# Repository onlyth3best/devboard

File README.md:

# devboard
a project for Fallout, made with help from stasis.hackclub.com/starter-projects/devboard
<br/> /kicad has relevant KiCad files, /3dmodels has the .STEP files, /prod has gerber files~
<br/>
<br/> "_A development board is a specially designed printed circuit board (PCB) that integrates a microcontroller or microprocessor along with essential components such as input/output pins, power supply interfaces, USB connectors, LEDs, and often onboard sensors._" ([source](https://regentelectronics.com/microcontrollers/what-is-a-development-board-introduction-types-and-applications))
<br/>
<br/>

<br/> Setup guide:
<br/>  - the only setup needed in this sense, if I understand correctly, is using the files in this repo to upload to JLCPCB or something similar in order to receive a physical version…
<br/>
<br/> Motivation:
<br/>  - Since I started hardware very very recently, I wanted to try my hand at something that was a little more challenging than a regular pcb but still within the realm of KiCad work. Additionally, I find routing very fun to do, hence why I had a lot of fun with this project in certain parts.

<br/> BOM:
<br/>
| Reference  | Qty | Value | approx price in USD | links I found, not sure if they're all 100% correct though :heavysob: |
| ------------- | ------------- | ------------- | ------------- | ------------- |
| C1, C10 | 2 | C_0402_1005Metric | 0.02 | [links](https://www.kondik.cz/cl05a105kp5nnnc/) |
| C2, C3, C4, C5, C6, C7, C8, C9, C11, C12 | 10 | C_0402_1005Metric | 0.10| [links](https://www.kondik.cz/cl05a105kp5nnnc/) |
| C13, C14 | 2 | C_0402_1005Metric | 0.02 | [links](https://www.kondik.cz/cc0402krx7r7bb104-kondenzator-keramicky-smd-0402-100nf-16v/) |
| C15, C16 | 2 | C_0402_1005Metric | 0.02 | [links](https://www.kondik.cz/cc0402krx7r7bb104-kondenzator-keramicky-smd-0402-100nf-16v/) |
| J1 | 1 | USB_C_Receptacle_HRO_TYPE-C-31-M-12 | 0.10–0.25 | [links](https://www.lcsc.com/product-detail/USB-Type-C_Korean-Hroparts-Elec-TYPE-C-31-M-12_C165948.html) |
| J2, J3 | 2 | PinHeader_1x20_P2.54mm_Vertical | 0.20–0.80 | [links](https://www.lcsc.com/search?q=1x20+2.54mm+pin+header) |
| J4 | 1 | R_0402_1005Metric | 0.01 | [links](https://www.lcsc.com/search?q=0402+resistor) |
| R1, R2 | 2 | R_0402_1005Metric | 0.02 | [links](https://www.digikey.com/en/products/filter/resistor-kits/129) |
| R3, R4 | 2 | R_0402_1005Metric | 0.02 | [links](https://www.digikey.com/en/products/filter/resistor-kits/129) |
| R5, R7 | 2 | R_0402_1005Metric | 0.02 | [links](https://www.digikey.com/en/products/filter/resistor-kits/129) |
| R6 | 1 | R_0402_1005Metric | 0.01 | [links](https://www.digikey.com/en/products/filter/resistor-kits/129) |
| SW1 | 1 | SW_Push_SPST_NO_Alps_SKRK | 0.10–0.50 | [links](https://www.lcsc.com/search?q=Alps+SKRK) |
| U1 | 1 | QFN-56-1EP_7x7mm_P0.4mm_EP3.2x3.2mm | 1.00–2.00 | [links](https://www.raspberrypi.com/products/rp2040) |
| U3 | 1 | SOIC-8_5.3x5.3mm_P1.27mm | 0.30–0.80 | [links](https://www.lcsc.com/product-detail/NOR-FLASH_Winbond-Elec-W25Q64JVSSIQ_C179171.html) |
| U4 | 1 | TO-92_Inline | 0.05–0.30 | [links](https://www.lcsc.com/product-detail/Bipolar-Transistors-BJT_ON-Semicon-2N3904_C20526.html) |
| Y1 | 1 | Crystal_SMD_3225-4Pin_3.2x2.5mm | 0.05–0.20  | [links](https://www.lcsc.com/product-detail/C13738.html) |
|  |  |  | total BOM price ~ 2.95, with JLCPCB cost it's around 5.95 USD |  |

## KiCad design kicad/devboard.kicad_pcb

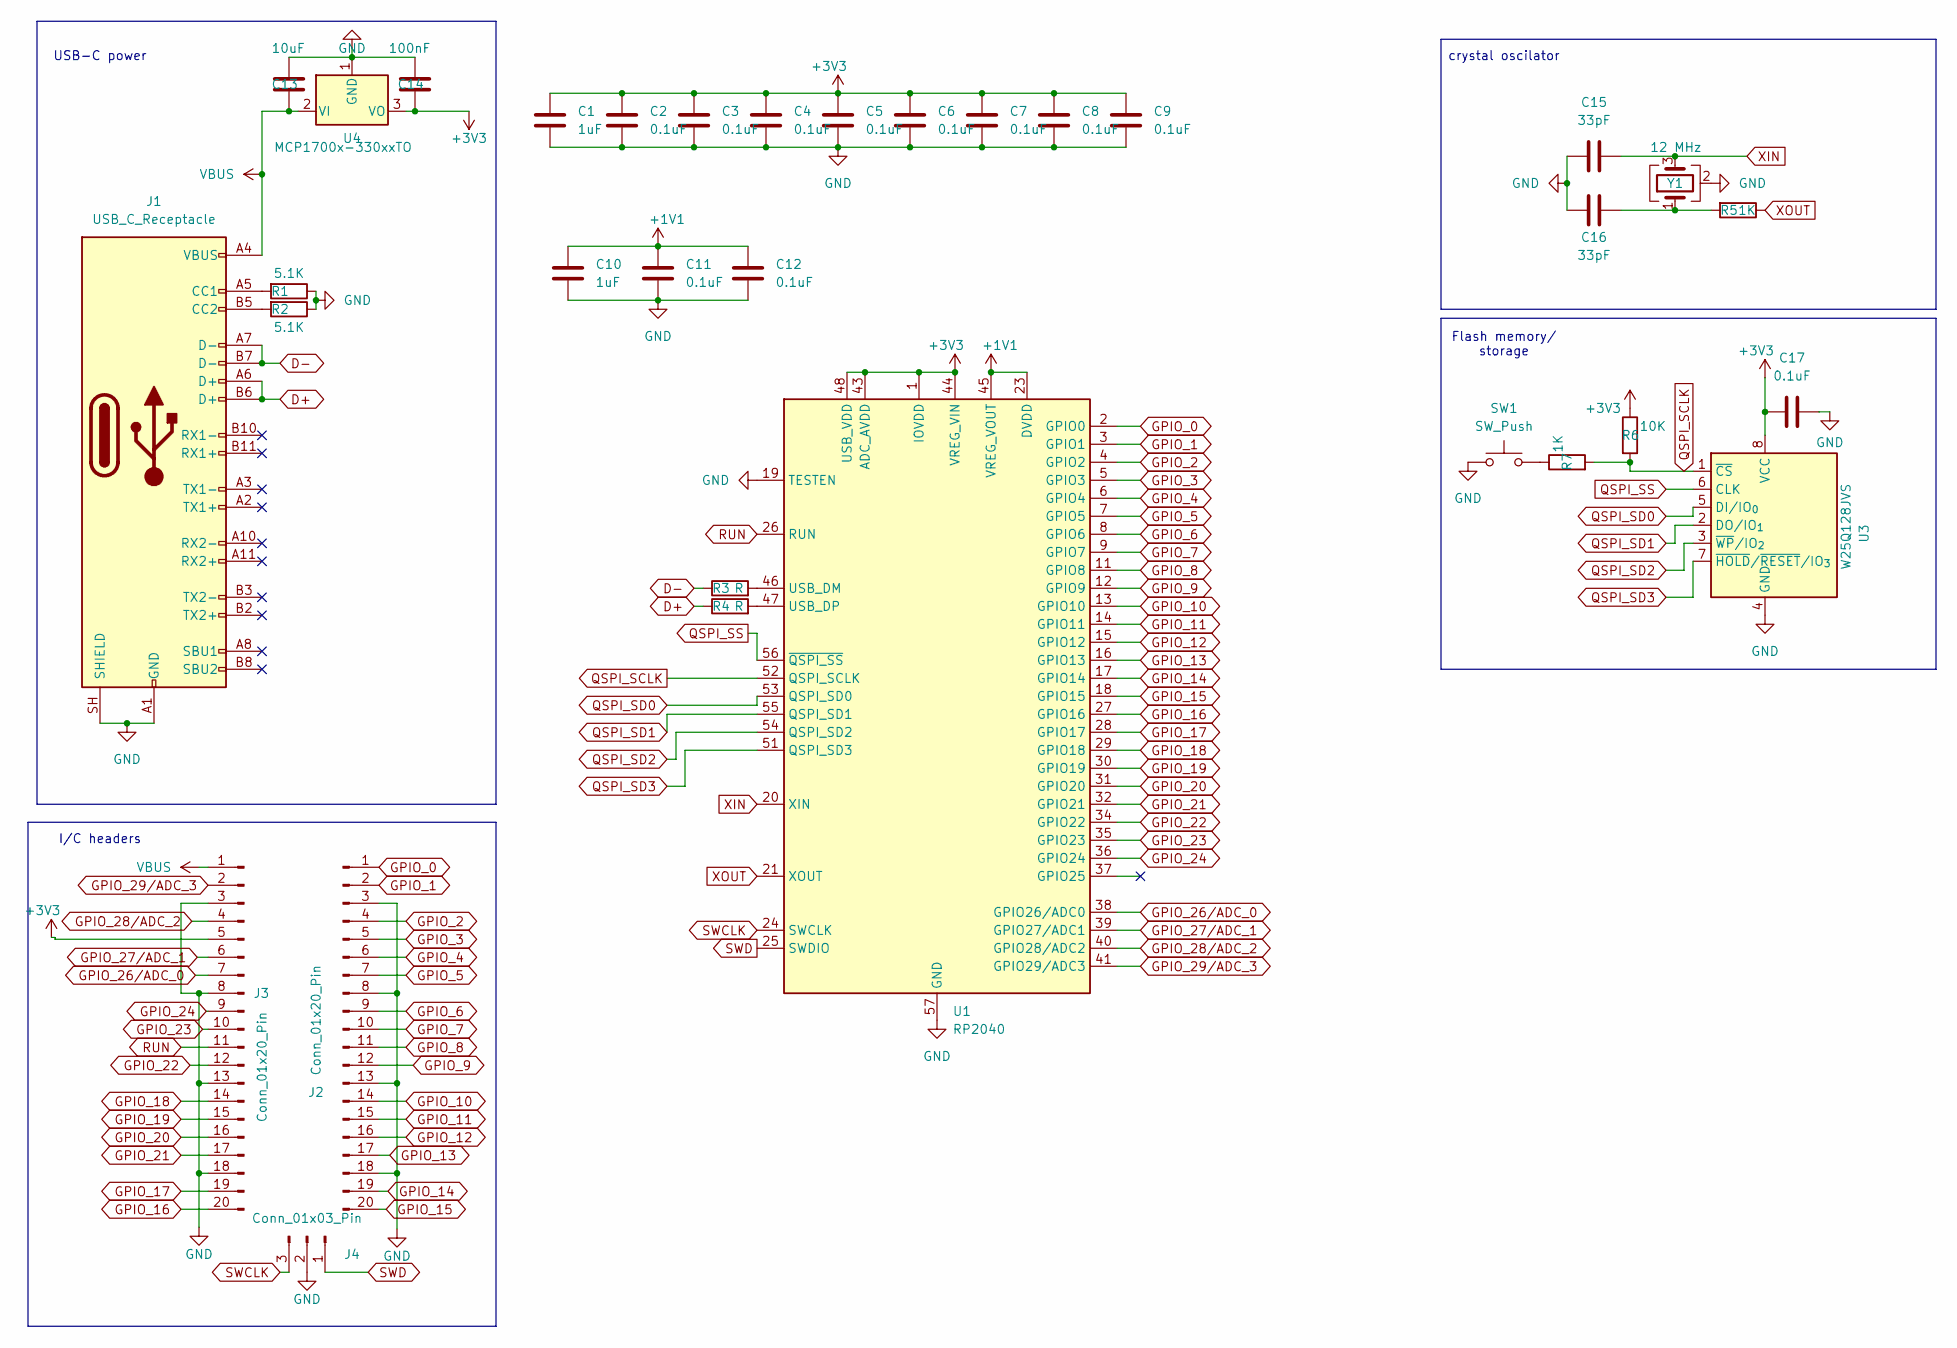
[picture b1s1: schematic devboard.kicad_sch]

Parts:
C1, C10: 1uF; C_0402_1005Metric
C2, C3, C4, C5, C6, C7, C8, C9, C11, C12, C17: 0.1uF; C_0402_1005Metric
C13: 10uF; C_0402_1005Metric
C14: 100nF; C_0402_1005Metric
C15, C16: 33pF; C_0402_1005Metric
J1: USB_C_Receptacle; USB_C_Receptacle_HRO_TYPE-C-31-M-12
J2, J3: Conn_01x20_Pin; PinHeader_1x20_P2.54mm_Vertical
J4: Conn_01x03_Pin; PinHeader_1x03_P2.54mm_Vertical
R1, R2: 5.1K; R_0402_1005Metric
R3, R4: R; R_0402_1005Metric
R5, R7: 1K; R_0402_1005Metric
R6: 10K; R_0402_1005Metric
SW1: SW_Push; SW_Push_SPST_NO_Alps_SKRK
U1: RP2040; QFN-56-1EP_7x7mm_P0.4mm_EP3.2x3.2mm
U3: W25Q128JVS; SOIC-8_5.3x5.3mm_P1.27mm
U4: MCP1700x-330xxTO; TO-92_Inline
Y1: 12 MHz; Crystal_SMD_3225-4Pin_3.2x2.5mm

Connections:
+1V1: C10.1, C11.1, C12.1, U1.23 (DVDD), U1.45 (VREG_VOUT), U1.50 (DVDD)
+3V3: C1.1, C2.1, C3.1, C4.1, C5.1, C6.1, C7.1, C8.1, C9.1, C14.2, C17.1, J3.5, R6.1, U1.1 (IOVDD), U1.10 (IOVDD), U1.22 (IOVDD), U1.33 (IOVDD), U1.42 (IOVDD), U1.43 (ADC_AVDD), U1.44 (VREG_VIN), U1.48 (USB_VDD), U1.49 (IOVDD), U3.8 (VCC), U4.3 (VO)
D+: J1.A6 (D+), J1.B6 (D+), R4.1
D-: J1.A7 (D-), J1.B7 (D-), R3.1
GND: C1.2, C2.2, C3.2, C4.2, C5.2, C6.2, C7.2, C8.2, C9.2, C10.2, C11.2, C12.2, C13.1, C14.1, C15.1, C16.1, C17.2, J1.A1 (GND), J1.A12 (GND), J1.B1 (GND), J1.B12 (GND), J1.SH (SHIELD), J2.3, J2.8, J2.13, J2.18, J3.3, J3.8, J3.13, J3.18, J4.2, R1.1, R2.1, SW1.1, U1.19 (TESTEN), U1.57 (GND), U3.4 (GND), U4.1 (GND), Y1.2 (G), Y1.4 (G)
GPIO_0: J2.1, U1.2 (GPIO0)
GPIO_1: J2.2, U1.3 (GPIO1)
GPIO_2: J2.4, U1.4 (GPIO2)
GPIO_3: J2.5, U1.5 (GPIO3)
GPIO_4: J2.6, U1.6 (GPIO4)
GPIO_5: J2.7, U1.7 (GPIO5)
GPIO_6: J2.9, U1.8 (GPIO6)
GPIO_7: J2.10, U1.9 (GPIO7)
GPIO_8: J2.11, U1.11 (GPIO8)
GPIO_9: J2.12, U1.12 (GPIO9)
GPIO_10: J2.14, U1.13 (GPIO10)
GPIO_11: J2.15, U1.14 (GPIO11)
GPIO_12: J2.16, U1.15 (GPIO12)
GPIO_13: J2.17, U1.16 (GPIO13)
GPIO_14: J2.19, U1.17 (GPIO14)
GPIO_15: J2.20, U1.18 (GPIO15)
GPIO_16: J3.20, U1.27 (GPIO16)
GPIO_17: J3.19, U1.28 (GPIO17)
GPIO_18: J3.14, U1.29 (GPIO18)
GPIO_19: J3.15, U1.30 (GPIO19)
GPIO_20: J3.16, U1.31 (GPIO20)
GPIO_21: J3.17, U1.32 (GPIO21)
GPIO_22: J3.12, U1.34 (GPIO22)
GPIO_23: J3.10, U1.35 (GPIO23)
GPIO_24: J3.9, U1.36 (GPIO24)
GPIO_26/ADC_0: J3.7, U1.38 (GPIO26/ADC0)
GPIO_27/ADC_1: J3.6, U1.39 (GPIO27/ADC1)
GPIO_28/ADC_2: J3.4, U1.40 (GPIO28/ADC2)
GPIO_29/ADC_3: J3.2, U1.41 (GPIO29/ADC3)
unnamed: C16.2, R5.2, Y1.1
unnamed: J1.A5 (CC1), R1.2
unnamed: J1.B5 (CC2), R2.2
unnamed: R7.1, SW1.2
unnamed: R3.2, U1.46 (USB_DM)
unnamed: R4.2, U1.47 (USB_DP)
QSPI_SCLK: R6.2, R7.2, U1.52 (QSPI_SCLK), U3.1 (~CS)
QSPI_SD0: U1.53 (QSPI_SD0), U3.5 (DI/IO_{0})
QSPI_SD1: U1.55 (QSPI_SD1), U3.2 (DO/IO_{1})
QSPI_SD2: U1.54 (QSPI_SD2), U3.3 (~WP/IO_{2})
QSPI_SD3: U1.51 (QSPI_SD3), U3.7 (~HOLD/~RESET/IO_{3})
QSPI_SS: U1.56 (~QSPI_SS), U3.6 (CLK)
RUN: J3.11, U1.26 (RUN)
SWCLK: J4.3, U1.24 (SWCLK)
SWD: J4.1, U1.25 (SWDIO)
VBUS: C13.2, J1.A4 (VBUS), J1.A9 (VBUS), J1.B4 (VBUS), J1.B9 (VBUS), J3.1, U4.2 (VI)
XIN: C15.2, U1.20 (XIN), Y1.3
XOUT: R5.1, U1.21 (XOUT)

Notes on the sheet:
Flash memory/ storage
USB-C power
crystal oscilator
I/C headers

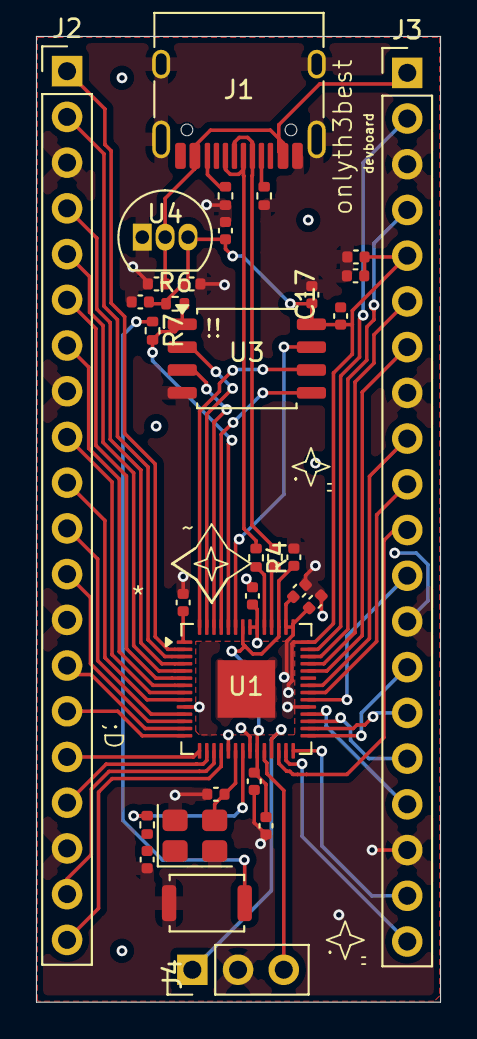
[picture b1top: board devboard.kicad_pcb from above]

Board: 2 copper layers, 22.4 x 53.7 mm, 33 parts (0 on the bottom side), 52 nets.

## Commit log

2026-05-06 Create test
